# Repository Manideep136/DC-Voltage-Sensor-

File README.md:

# DC-Voltage-Sensor

# High DC Voltage Sensor PCB Using KiCad

## 📌 Project Overview

This project focuses on designing a **High DC Voltage Sensor PCB** using KiCad. The circuit is intended to measure a DC voltage higher than the input range of a microcontroller or measurement device by scaling the voltage to a suitable level.

A resistor voltage divider is a common method for reducing a high DC voltage to a lower proportional voltage. The scaled output can then be measured using a suitable analog-to-digital converter (ADC), microcontroller, or measurement instrument.

This project demonstrates voltage sensing, resistor selection, schematic design, footprint assignment, and PCB layout using KiCad.

## 🎯 Objectives

- Understand the principle of high DC voltage measurement.
- Learn how a resistor voltage divider works.
- Design a DC voltage sensing circuit.
- Create the schematic using KiCad.
- Assign suitable footprints to electronic components.
- Design and route the PCB.
- Perform Electrical Rules Check (ERC) and Design Rules Check (DRC).
- Inspect the completed PCB using KiCad's 3D Viewer.

## ⚙️ Working Principle

The sensor scales the input DC voltage using a resistor network.

The voltage divider consists of two resistors connected in series across the input voltage. The output is measured across the lower resistor.

The voltage divider equation is:

```text
Vout = Vin × R2 / (R1 + R2)
```

Where:

- `Vin` = Input DC voltage.
- `Vout` = Scaled output voltage.
- `R1` = Upper resistor of the voltage divider.
- `R2` = Lower resistor of the voltage divider.

When a high DC voltage is applied, the resistor network reduces it to a lower voltage proportional to the input.

The output can be connected to a measurement circuit, provided the output voltage remains within the permitted input range of that circuit.

**Note:** The actual resistor values, maximum input voltage, output range, and protection components must match the circuit shown in the reference design.

## 🔌 Block Diagram

```text
     High DC Voltage Input
              |
              v
      Resistor Divider
              |
              v
      Scaled DC Voltage
              |
              v
      Measurement Circuit
              |
              v
       Voltage Reading
```

## 🧩 Components Used

The final bill of materials depends on the actual schematic.

| Component | Function |
|---|---|
| R1 | Upper voltage-divider resistor |
| R2 | Lower voltage-divider resistor |
| Input connector | Connects the DC voltage source |
| Output connector | Provides the scaled voltage output |
| Protection components | Help protect the measurement circuit, if included |
| Filter capacitor | Reduces noise, if included |

Additional resistors, capacitors, diodes, or active components may be required depending on the reference circuit.

## 🖥️ PCB Design Using KiCad

The PCB design process includes:

1. Creating a new KiCad project.
2. Drawing the high DC voltage sensor schematic.
3. Adding the required components.
4. Connecting the voltage-divider network.
5. Assigning suitable footprints.
6. Updating the PCB from the schematic.
7. Arranging the components on the PCB.
8. Routing the copper tracks.
9. Running ERC in the schematic editor.
10. Running DRC in the PCB editor.
11. Inspecting the final PCB using the 3D Viewer.

## 📁 Project Structure

```text
High-DC-Voltage-Sensor/
├── High-DC-Voltage-Sensor.kicad_pro
├── High-DC-Voltage-Sensor.kicad_sch
├── High-DC-Voltage-Sensor.kicad_pcb
├── README.md
└── Images/
    ├── schematic.png
    ├── pcb_layout.png
    └── 3d_view.png
```

## 📐 PCB Design Considerations

- Select resistor values according to the intended input voltage range.
- Check the voltage rating and power dissipation of each resistor.
- Consider using multiple series resistors when a single resistor cannot safely withstand the voltage.
- Ensure the scaled output never exceeds the connected ADC or instrument's input limits.
- Add suitable input protection where required by the design.
- Choose connectors rated for the intended voltage and current.
- Maintain suitable PCB creepage and clearance distances.
- Use suitable track widths and appropriate PCB materials for the voltage involved.

## 🧪 Testing Procedure

1. Inspect the PCB for solder bridges and incorrect connections.
2. Verify resistor values and component orientation.
3. Check the input and output connector pin assignments.
4. Run ERC and DRC in KiCad.
5. Begin testing with a safe, current-limited, low-voltage DC source.
6. Measure the input voltage with a suitable multimeter.
7. Measure the divider output voltage.
8. Compare the measured output with the calculated voltage-divider output.
9. Check the scaling accuracy before connecting any microcontroller or ADC.

Testing at higher voltages should only be performed with properly rated equipment and a design that has been reviewed for electrical safety.

## ⚠️ Safety Precautions

**High DC voltage can cause serious injury or death.**

- Do not touch the circuit while it is energized.
- Do not connect an unverified high-voltage circuit directly to a microcontroller.
- Check resistor voltage ratings, power ratings, insulation, and PCB spacing.
- Use appropriate fusing, enclosures, and protection.
- Discharge capacitors safely before handling the circuit.
- Do not assume that a voltage divider provides electrical isolation.
- Test with low voltage first and obtain qualified review before high-voltage operation.

## 🚀 Future Improvements

- Add an LCD or OLED voltage display.
- Interface the sensor with an Arduino or other suitable microcontroller.
- Add overvoltage protection.
- Improve measurement accuracy through calibration.
- Add filtering to reduce noise.
- Include a connector for data logging.
- Develop a digital voltage monitoring system.

## 📚 Learning Outcomes

Through this project, I learned:

- Principles of DC voltage measurement.
- Voltage-divider calculations.
- Resistor voltage and power ratings.
- Schematic design using KiCad.
- Footprint assignment.
- PCB component placement and routing.
- ERC and DRC verification.
- Basic PCB safety considerations.
- Testing and calibration of voltage-sensing circuits.

## 🛠️ Software Used

**KiCad 9.0**

This project is intended for educational and learning purposes. The circuit must be verified against the actual schematic and tested safely before practical use.

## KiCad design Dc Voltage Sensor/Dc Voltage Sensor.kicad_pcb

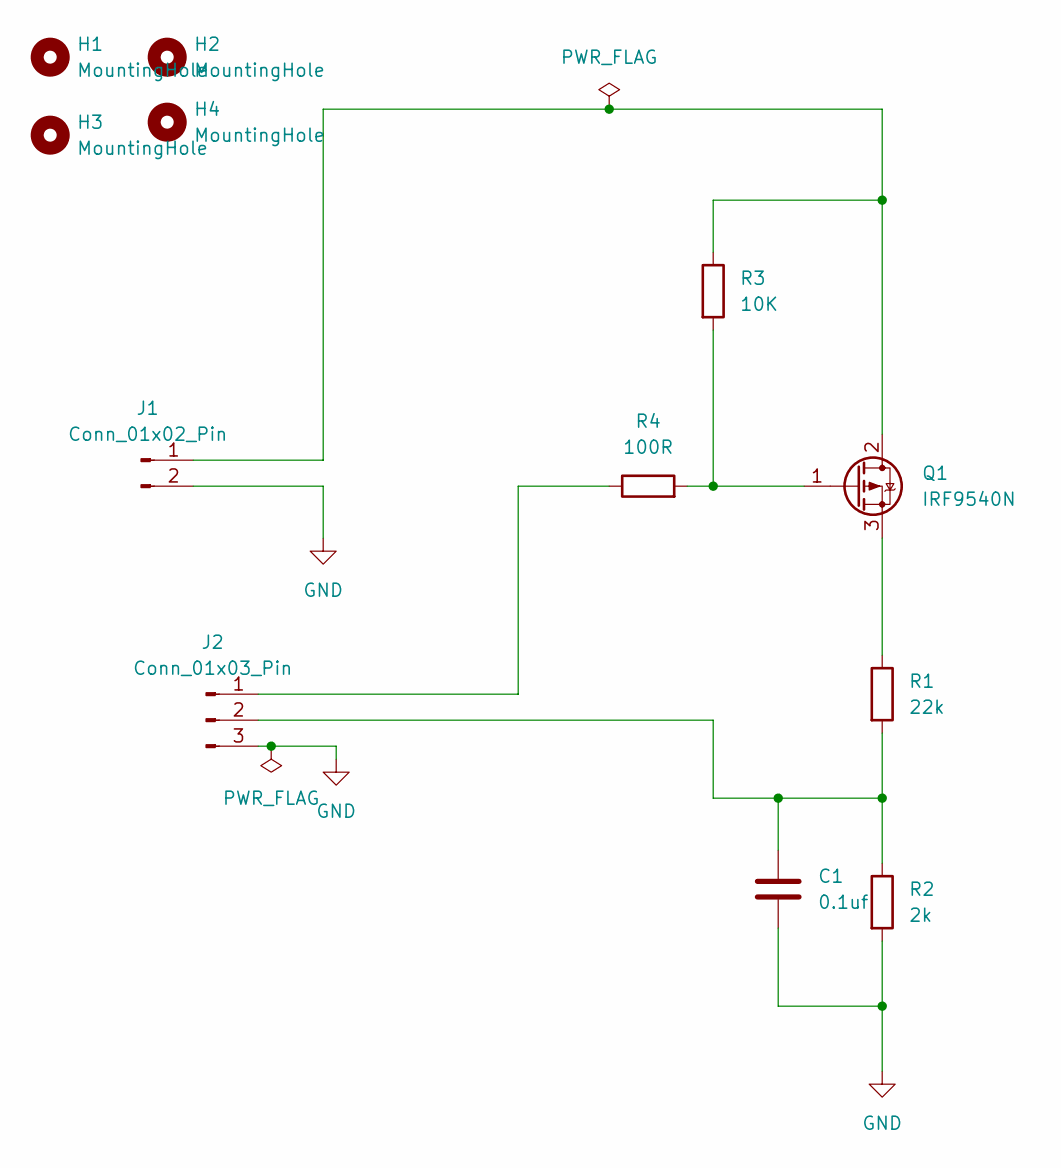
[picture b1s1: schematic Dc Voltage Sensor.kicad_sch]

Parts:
C1: 0.1uf; C_Disc_D6.0mm_W2.5mm_P5.00mm
H1, H2, H3, H4: MountingHole; MountingHole_2.2mm_M2_ISO7380_Pad_TopOnly
J1: Conn_01x02_Pin; TerminalBlock_Philmore_TB132_1x02_P5.00mm_Horizontal
J2: Conn_01x03_Pin; PinHeader_1x03_P2.54mm_Horizontal
Q1: IRF9540N; TO-220-3_Vertical
R1: 22k; R_Axial_DIN0204_L3.6mm_D1.6mm_P7.62mm_Horizontal
R2: 2k; R_Axial_DIN0204_L3.6mm_D1.6mm_P7.62mm_Horizontal
R3: 10K; R_Axial_DIN0204_L3.6mm_D1.6mm_P7.62mm_Horizontal
R4: 100R; R_Axial_DIN0204_L3.6mm_D1.6mm_P7.62mm_Horizontal

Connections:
GND: C1.2, J1.2, J2.3, R2.2
unnamed: J1.1, Q1.2 (D), R3.1
unnamed: J2.1, R4.1
unnamed: C1.1, J2.2, R1.2, R2.1
unnamed: Q1.1 (G), R3.2, R4.2
unnamed: Q1.3 (S), R1.1

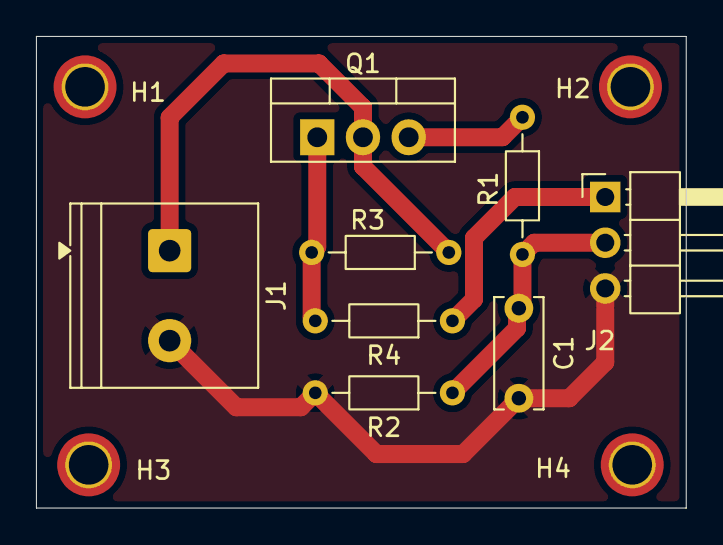
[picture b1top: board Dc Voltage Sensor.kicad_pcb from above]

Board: 2 copper layers, 36.1 x 26.2 mm, 12 parts (0 on the bottom side), 6 nets.
